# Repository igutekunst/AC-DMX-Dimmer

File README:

An AC DMX512 dimmer board that can dim 6 resistive loads.

WARNING: This design is dangerous, somewhat untested, and uses line voltage. Do not build. For reference purposes only.

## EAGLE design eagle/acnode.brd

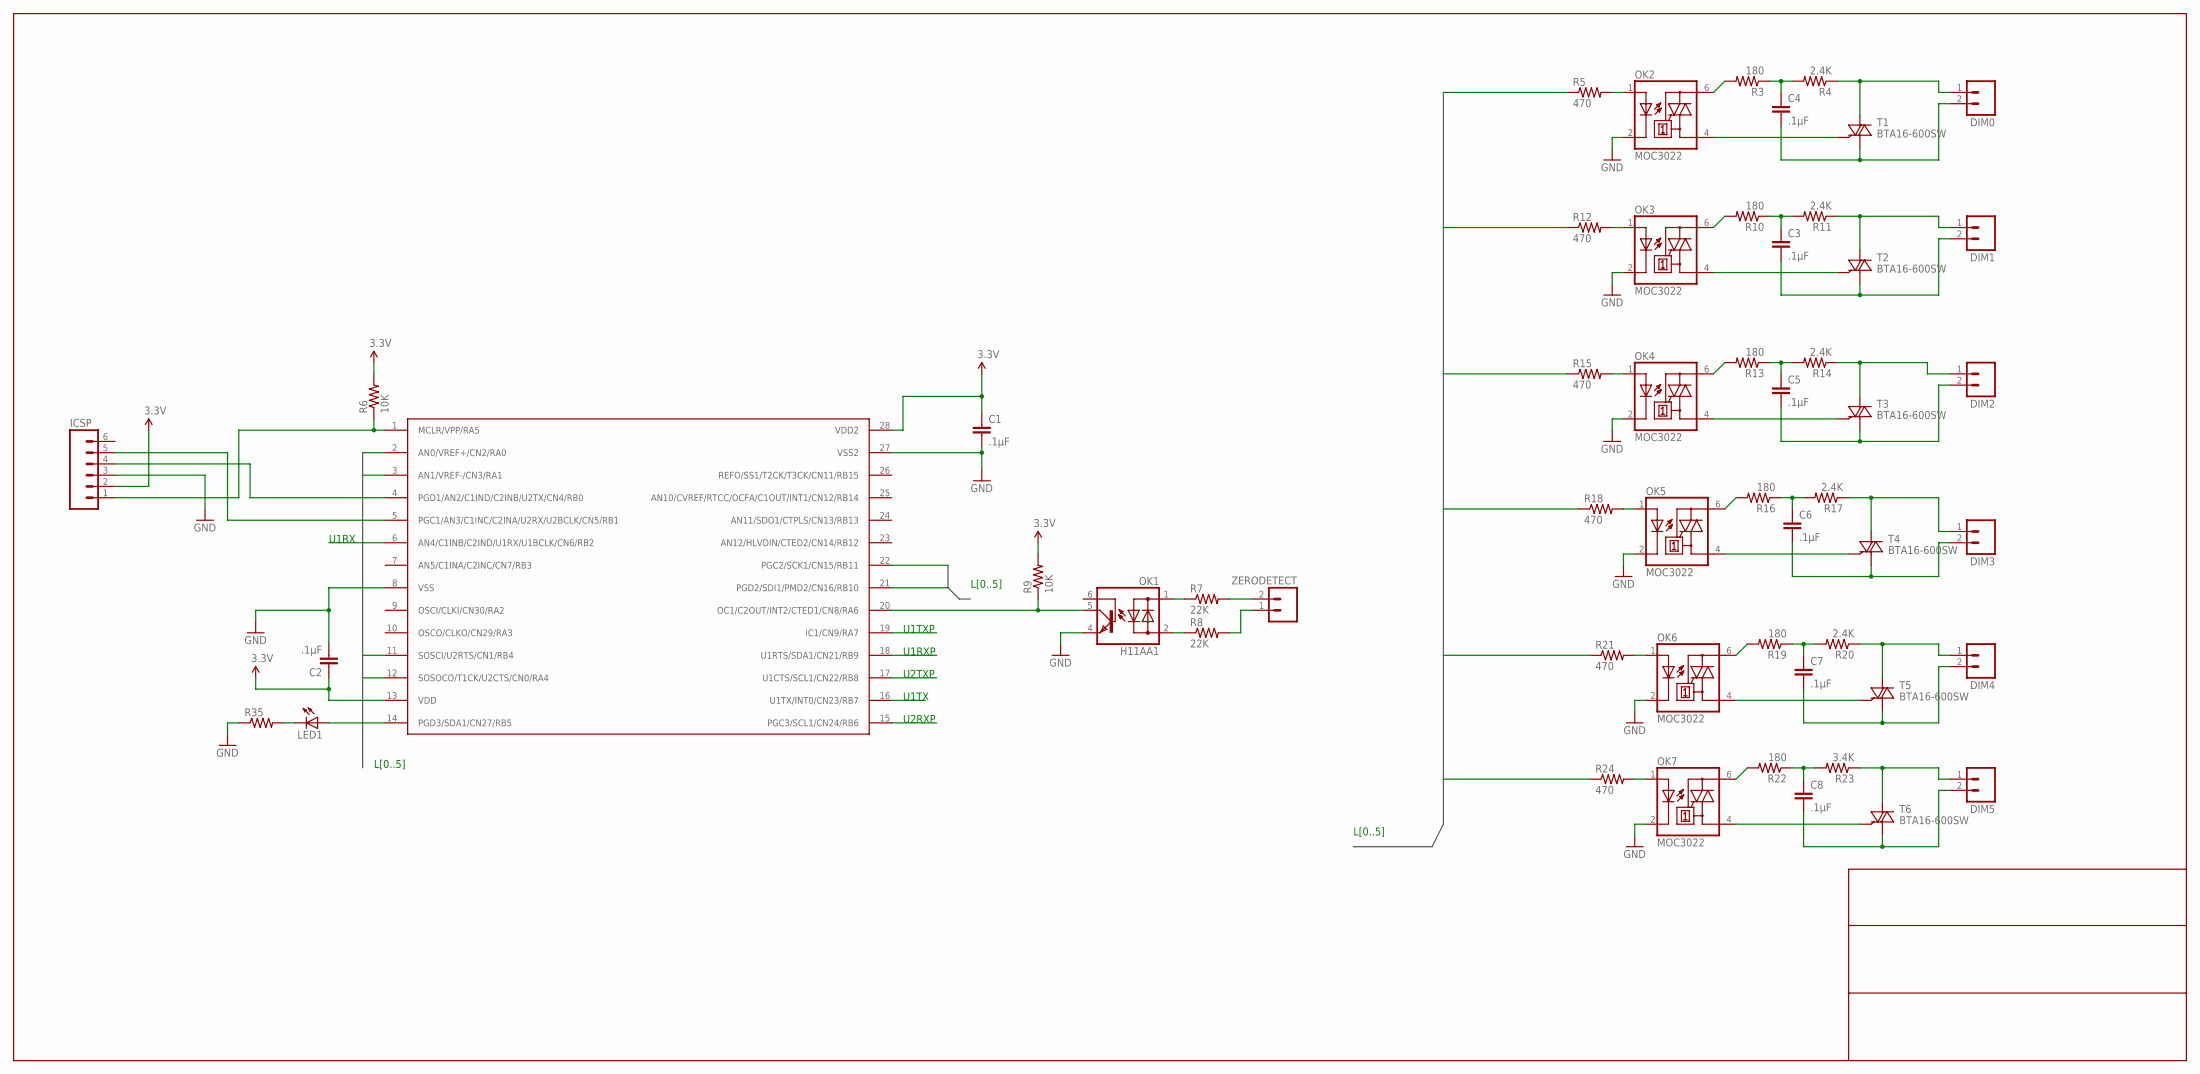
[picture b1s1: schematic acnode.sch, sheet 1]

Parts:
C1, C2: .1µF; 1206
C3, C4, C5, C6, C7, C8: .1µF; CAP-PTH-5MM
DIM0, DIM1, DIM2, DIM3, DIM4, DIM5: M025MM; SCREWTERMINAL-5MM-2
ICSP: M06LOCK; 1X06_LOCK
LED1: LEDCHIPLED_1206; CHIPLED_1206
OK1: H11AA1; DIL06
OK2, OK3, OK4, OK5, OK6, OK7: MOC3022; DIL06
R3, R10, R13, R16, R19, R22: 180; AXIAL-0.4
R4, R11, R14, R17, R20: 2.4K; AXIAL-0.4
R5, R12, R15, R18, R21, R24: 470; 1206
R6, R9: 10K; 1206
R7, R8: 22K; AXIAL-0.4
R23: 3.4K; AXIAL-0.4
R35: RESISTOR1206; 1206
T1, T2, T3, T4, T5, T6: BTA16-600SW; TO220BV
U$2: PIC24F16KA102; SSOP28DB
ZERODETECT: M025MM; SCREWTERMINAL-5MM-2

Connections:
3.3V: C1.1, C2.1, ICSP.2, R6.2, R9.2, U$2.13 (VDD), U$2.28 (VDD2); also elsewhere on the board
GND: C1.2, C2.2, ICSP.3, OK1.4 (E), OK2.2 (C), OK3.2 (C), OK4.2 (C), OK5.2 (C), OK6.2 (C), OK7.2 (C), R35.1, U$2.8 (VSS), U$2.27 (VSS2); also elsewhere on the board
L0: R5.1, U$2.2 (AN0/VREF+/CN2/RA0)
L1: R12.1, U$2.3 (AN1/VREF-/CN3/RA1)
L2: R15.1, U$2.22 (PGC2/SCK1/CN15/RB11)
L3: R18.1, U$2.21 (PGD2/SDI1/PMD2/CN16/RB10)
L4: R21.1, U$2.11 (SOSCI/U2RTS/CN1/RB4)
L5: R24.1, U$2.12 (SOSOCO/T1CK/U2CTS/CN0/RA4)
unnamed: LED1.A, U$2.14 (PGD3/SDA1/CN27/RB5)
unnamed: OK3.4 (A1), T2.G
unnamed: ICSP.1, R6.1, U$2.1 (MCLR/VPP/RA5)
unnamed: LED1.C, R35.2
unnamed: OK2.4 (A1), T1.G
unnamed: OK2.6 (A2), R3.P$2 (2)
unnamed: C4.1, R3.P$1 (1), R4.P$2 (2)
unnamed: C4.2, DIM0.2, T1.T1 (A1)
unnamed: DIM0.1, R4.P$1 (1), T1.T2 (A2)
unnamed: OK2.1 (A), R5.2
unnamed: OK1.1 (AC1), R7.P$1 (1)
unnamed: OK1.2 (AC2), R8.P$1 (1)
unnamed: OK1.5 (C), R9.1, U$2.20 (OC1/C2OUT/INT2/CTED1/CN8/RA6)
unnamed: OK3.6 (A2), R10.P$2 (2)
unnamed: C3.1, R10.P$1 (1), R11.P$2 (2)
unnamed: C3.2, DIM1.2, T2.T1 (A1)
unnamed: DIM1.1, R11.P$1 (1), T2.T2 (A2)
unnamed: OK3.1 (A), R12.2
unnamed: OK4.4 (A1), T3.G
unnamed: OK4.6 (A2), R13.P$2 (2)
unnamed: C5.1, R13.P$1 (1), R14.P$2 (2)
unnamed: C5.2, DIM2.2, T3.T1 (A1)
unnamed: DIM2.1, R14.P$1 (1), T3.T2 (A2)
unnamed: OK4.1 (A), R15.2
unnamed: OK5.4 (A1), T4.G
unnamed: OK5.6 (A2), R16.P$2 (2)
unnamed: C6.1, R16.P$1 (1), R17.P$2 (2)
unnamed: C6.2, DIM3.2, T4.T1 (A1)
unnamed: DIM3.1, R17.P$1 (1), T4.T2 (A2)
unnamed: OK5.1 (A), R18.2
unnamed: OK6.4 (A1), T5.G
unnamed: OK6.6 (A2), R19.P$2 (2)
unnamed: C7.1, R19.P$1 (1), R20.P$2 (2)
unnamed: C7.2, DIM4.2, T5.T1 (A1)
unnamed: DIM4.1, R20.P$1 (1), T5.T2 (A2)
unnamed: OK6.1 (A), R21.2
unnamed: OK7.4 (A1), T6.G
unnamed: OK7.6 (A2), R22.P$2 (2)
unnamed: C8.1, R22.P$1 (1), R23.P$2 (2)
unnamed: C8.2, DIM5.2, T6.T1 (A1)
unnamed: DIM5.1, R23.P$1 (1), T6.T2 (A2)
unnamed: OK7.1 (A), R24.2
unnamed: R7.P$2 (2), ZERODETECT.2
unnamed: R8.P$2 (2), ZERODETECT.1
U1RX: U$2.6 (AN4/C1INB/C2IND/U1RX/U1BCLK/CN6/RB2); also elsewhere on the board
U1RXP: U$2.18 (U1RTS/SDA1/CN21/RB9); also elsewhere on the board
U1TX: U$2.16 (U1TX/INT0/CN23/RB7); also elsewhere on the board
U1TXP: U$2.19 (IC1/CN9/RA7); also elsewhere on the board
U2RX: ICSP.5, U$2.5 (PGC1/AN3/C1INC/C2INA/U2RX/U2BCLK/CN5/RB1); also elsewhere on the board
U2RXP: U$2.15 (PGC3/SCL1/CN24/RB6); also elsewhere on the board
U2TX: ICSP.4, U$2.4 (PGD1/AN2/C1IND/C2INB/U2TX/CN4/RB0); also elsewhere on the board
U2TXP: U$2.17 (U1CTS/SCL1/CN22/RB8); also elsewhere on the board

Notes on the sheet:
U1RX
U1TX
L[0..5]
U1TXP
U1RXP
U2TXP
U2RXP

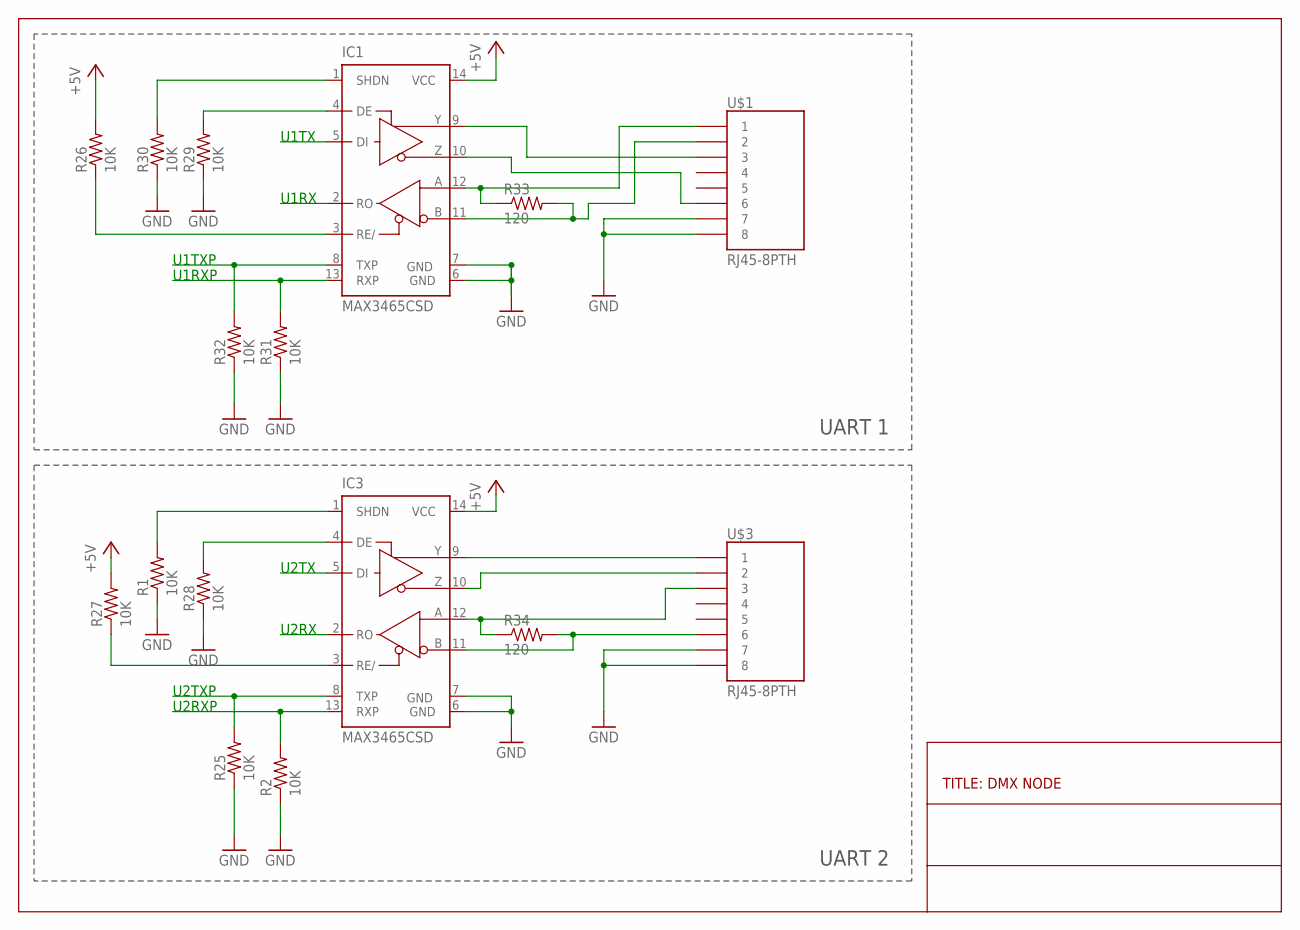
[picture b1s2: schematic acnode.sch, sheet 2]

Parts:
IC1, IC3: MAX3465CSD; SO14
R1, R2, R25, R26, R27, R28, R29, R30, R31, R32: 10K; 1206
R33, R34: 120; 1206
U$1, U$3: RJ45-8PTH; RJ45-8

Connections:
2A: IC3.12 (A), R34.1, U$3.3
2A1: IC1.12 (A), R33.1, U$1.1
2B: IC3.11 (B), R34.2, U$3.6
2B1: IC1.11 (B), R33.2, U$1.2
2Y: IC3.9 (Y), U$3.1
2Y1: IC1.9 (Y), U$1.3
2Z: IC3.10 (Z), U$3.2
+5V: IC1.14 (VCC), IC3.14 (VCC), R26.2, R27.2; also elsewhere on the board
GND: IC1.6 (GND), IC1.7 (GND), IC3.6 (GND), IC3.7 (GND), R1.1, R2.1, R25.1, R28.1, R29.1, R30.1, R31.1, R32.1, U$1.7, U$1.8, U$3.7, U$3.8; also elsewhere on the board
unnamed: IC3.1 (SHDN), R1.2
unnamed: IC1.4 (DE), R29.2
unnamed: IC1.3 (RE/), R26.1
unnamed: IC1.1 (SHDN), R30.2
unnamed: IC1.10 (Z), U$1.6
unnamed: IC3.4 (DE), R28.2
unnamed: IC3.3 (RE/), R27.1
U1RX: IC1.2 (RO); also elsewhere on the board
U1RXP: IC1.13 (RXP), R31.2; also elsewhere on the board
U1TX: IC1.5 (DI); also elsewhere on the board
U1TXP: IC1.8 (TXP), R32.2; also elsewhere on the board
U2RX: IC3.2 (RO); also elsewhere on the board
U2RXP: IC3.13 (RXP), R2.2; also elsewhere on the board
U2TX: IC3.5 (DI); also elsewhere on the board
U2TXP: IC3.8 (TXP), R25.2; also elsewhere on the board

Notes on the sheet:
TITLE: DMX NODE
U2TX
U2RX
U2TXP
U2RXP
U1RX
U1TX
U1TXP
U1RXP
UART 1
UART 2

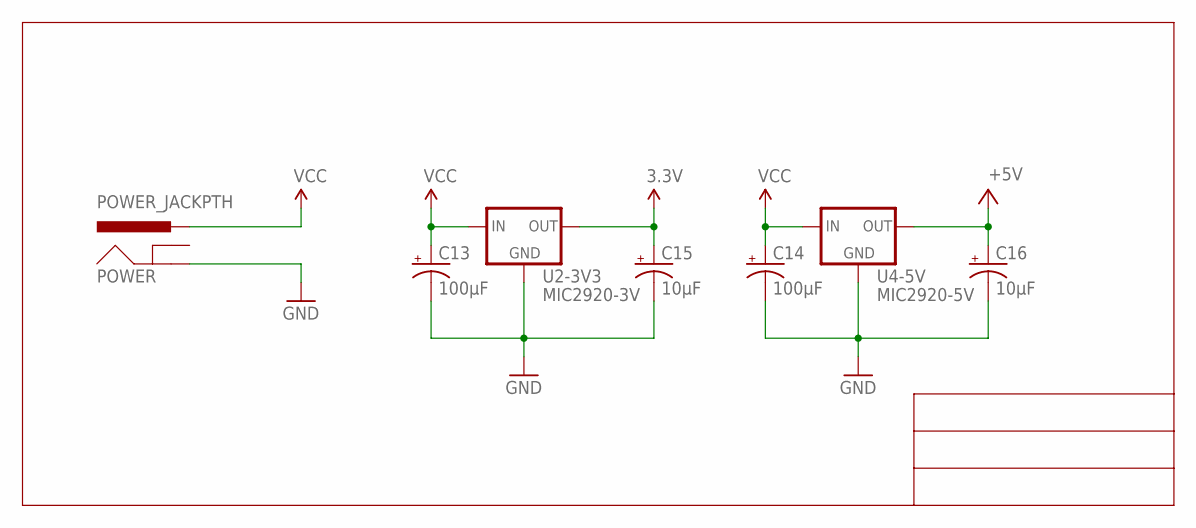
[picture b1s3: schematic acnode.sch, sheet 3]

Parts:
C13, C14: 100µF; CPOL-RADIAL-100UF-25V
C15, C16: 10µF; CPOL-RADIAL-10UF-25V
POWER: POWER_JACKPTH; POWER_JACK_PTH
U2-3V3: MIC2920-3V; SOT223
U4-5V: MIC2920-5V; SOT223

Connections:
3.3V: C15.1 (+), U2-3V3.3 (OUT); also elsewhere on the board
+5V: C16.1 (+), U4-5V.3 (OUT); also elsewhere on the board
GND: C13.2 (-), C14.2 (-), C15.2 (-), C16.2 (-), POWER.GND, U2-3V3.2 (GND), U4-5V.2 (GND); also elsewhere on the board
VCC: C13.1 (+), C14.1 (+), POWER.PWR, U2-3V3.1 (IN), U4-5V.1 (IN)

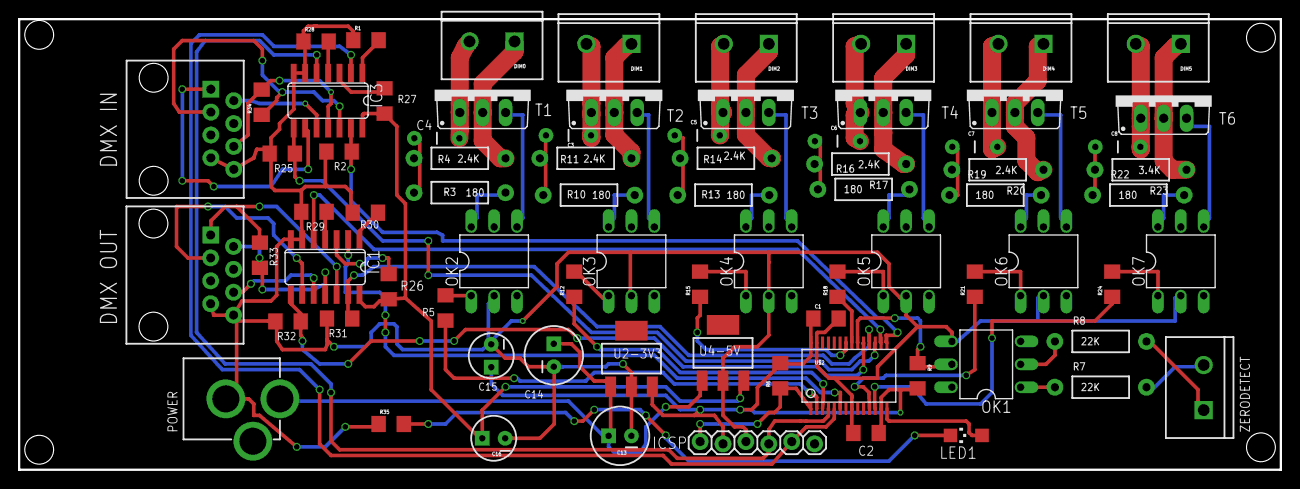
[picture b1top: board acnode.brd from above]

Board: 2 copper layers, 140.0 x 50.0 mm, 77 parts (0 on the bottom side), 76 nets.

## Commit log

2012-02-25 added .gitignore So they don't ruin your life
2013-09-28 Fixed power to MAX3465 bug
